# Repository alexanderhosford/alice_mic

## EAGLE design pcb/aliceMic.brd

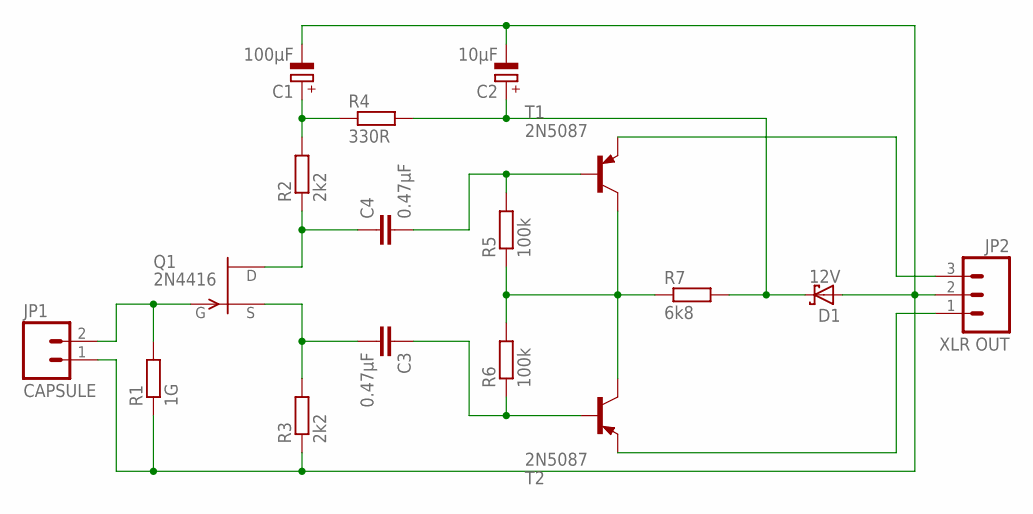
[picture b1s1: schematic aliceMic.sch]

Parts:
C1: 100µF; E22-10
C2: 10µF; E15-5
C3, C4: 0.47µF; C050-025X075
D1: 12V; CB417-15
JP1: CAPSULE; SCREWTERMINAL-3.5MM-2
JP2: XLR OUT; SCREWTERMINAL-3.5MM-3
Q1: 2N4416; TO92-
R1: 1G; 0207/10
R2, R3: 2k2; 0207/10
R4: 330R; 0207/10
R5, R6: 100k; 0207/10
R7: 6k8; 0207/10
T1, T2: 2N5087; TO92-EBC

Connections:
unnamed: C1.-, C2.-, D1.A, JP1.1, JP2.2, R1.1, R3.1
unnamed: C2.+, D1.C, R4.2, R7.2
unnamed: R5.1, R6.2, R7.1, T1.C, T2.C
unnamed: JP2.3, T1.E
unnamed: JP2.1, T2.E
unnamed: C4.2, R5.2, T1.B
unnamed: C3.1, R6.1, T2.B
unnamed: C1.+, R2.2, R4.1
unnamed: C4.1, Q1.3 (D), R2.1
unnamed: C3.2, Q1.2 (S), R3.2
unnamed: JP1.2, Q1.1 (G), R1.2

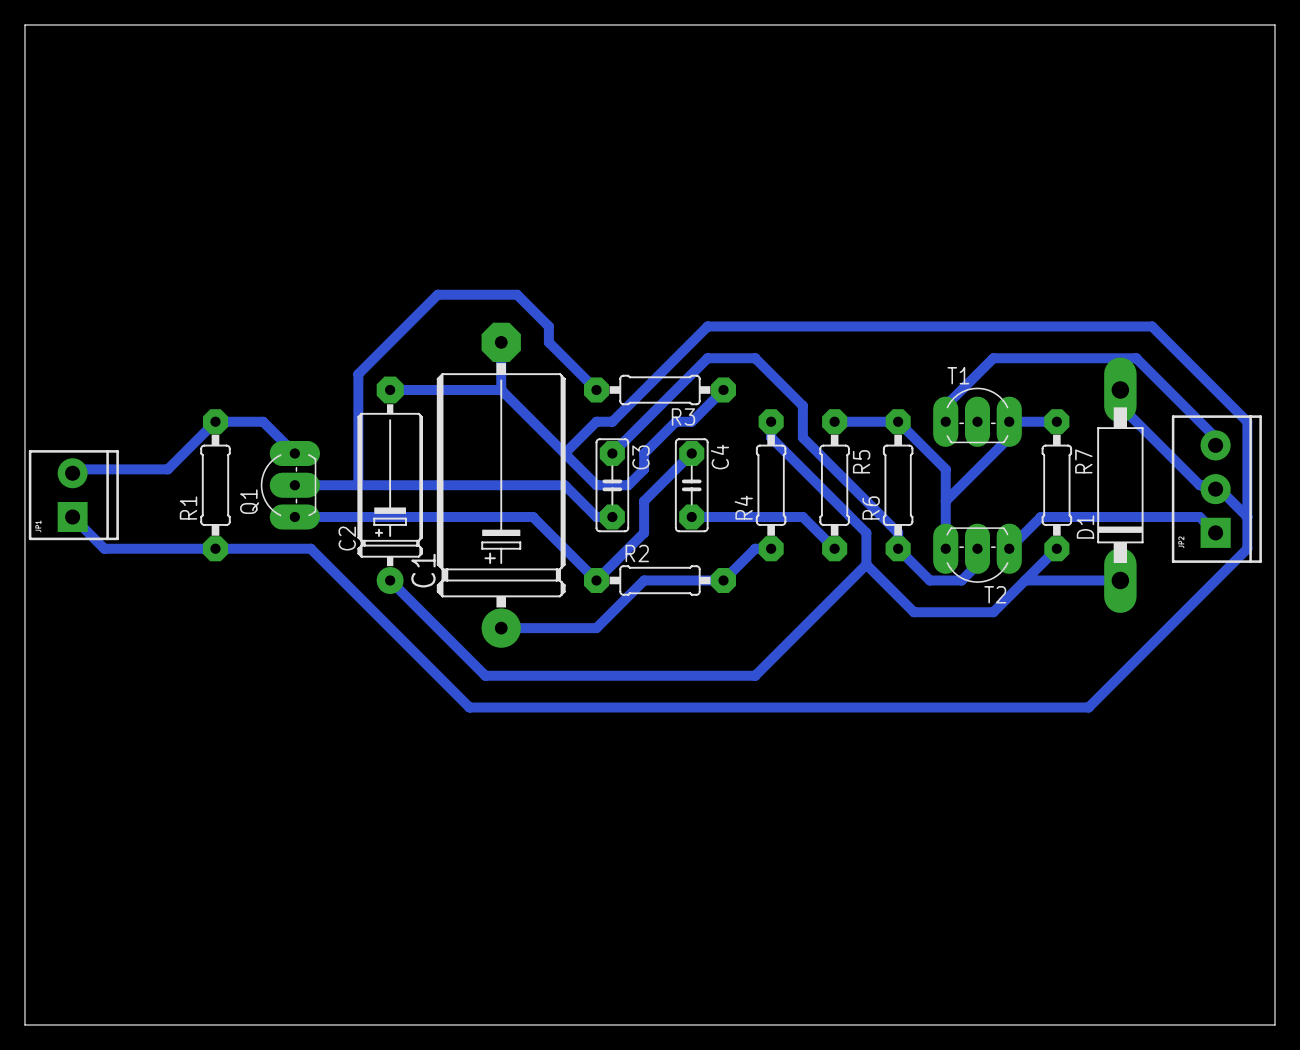
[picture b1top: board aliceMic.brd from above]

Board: 2 copper layers, 100.0 x 80.0 mm, 17 parts (0 on the bottom side), 11 nets.

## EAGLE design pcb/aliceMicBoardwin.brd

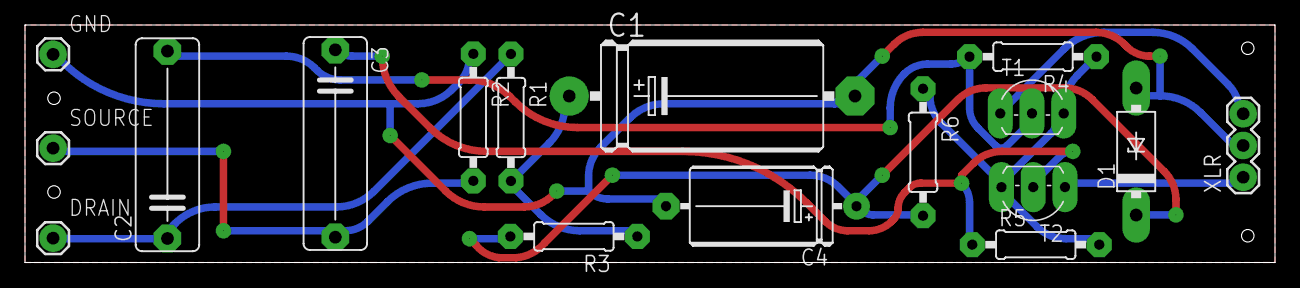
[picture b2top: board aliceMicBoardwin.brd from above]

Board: 2 copper layers, 100.0 x 19.0 mm, 17 parts (0 on the bottom side), 10 nets.

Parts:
C1: 100µF; E22-9
C2, C3: 0.47µF; C150-045X170
C4: 10µF; E15-6
D1: 12V; F126Z10
DRAIN: 1X01
GND: 1X01
R1, R2: 2k2; 0207/10
R3: 330R; 0207/10
R4, R5: 100k; 0207/10
R6: 6k8; 0207/10
SOURCE: 1X01
T1, T2: 2N5087; TO92-EBC
XLR: 1X03

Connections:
GND: C1.-, C4.-, D1.A, GND.1, R2.1, XLR.2
unnamed: C4.+, D1.C, R3.2, R6.2
unnamed: R4.1, R5.2, R6.1, T1.C, T2.C
unnamed: T1.E, XLR.3
unnamed: T2.E, XLR.1
unnamed: C2.2, R4.2, T1.B
unnamed: C3.1, R5.1, T2.B
unnamed: C1.+, R1.2, R3.1
unnamed: C2.1, DRAIN.1, R1.1
unnamed: C3.2, R2.2, SOURCE.1

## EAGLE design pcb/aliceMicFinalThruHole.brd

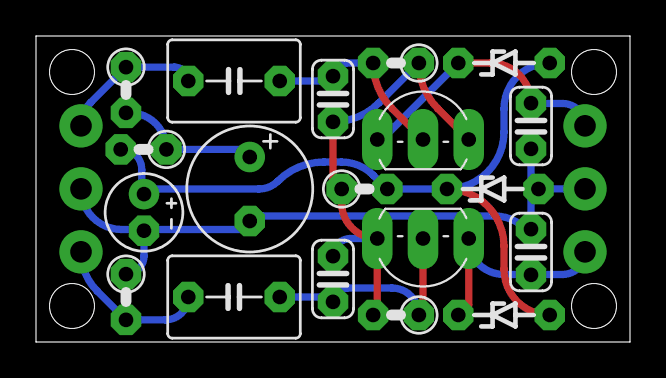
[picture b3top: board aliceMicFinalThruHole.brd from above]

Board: 2 copper layers, 33.0 x 17.0 mm, 21 parts (0 on the bottom side), 10 nets.

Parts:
C1: 100µ; E3,5-8
C2, C3: µ47; C050-045X075
C4: 10µ; E2-4
C5, C6: 470p; C025-024X044
C7, C8: 22n; C025-024X044
D1, D5: 6V; ZD-5-SMALLSILK
D4: 12V; ZD-5-SMALLSILK
FET_D_S_1G: 3.5MM_PADS
R1, R2: 2k2; 0207/2V
R3: 330R; 0207/2V
R4, R5: 100k; 0207/2V
R6: 6k8; 0207/2V
T1, T2: 2N5087; TO92-EBC
XLR: 3.5MM_PADS

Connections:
GND: C1.-, C4.-, C7.2, C8.1, D4.A, FET_D_S_1G.2, R2.1, XLR.2
unnamed: C4.+, D1.A, D4.C, D5.A, R3.2, R6.2
unnamed: C5.2, C6.1, R4.1, R5.2, R6.1, T1.C, T2.C
unnamed: C7.1, D1.C, T1.E, XLR.3
unnamed: C8.2, D5.C, T2.E, XLR.1
unnamed: C2.2, C5.1, R4.2, T1.B
unnamed: C3.1, C6.2, R5.1, T2.B
unnamed: C1.+, R1.2, R3.1
unnamed: C2.1, FET_D_S_1G.3, R1.1
unnamed: C3.2, FET_D_S_1G.1, R2.2

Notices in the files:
parts and their libraries:
SparkFun: Licensing: CC v3.0 Share-Alike You are welcome to use this library for commercial purposes.
